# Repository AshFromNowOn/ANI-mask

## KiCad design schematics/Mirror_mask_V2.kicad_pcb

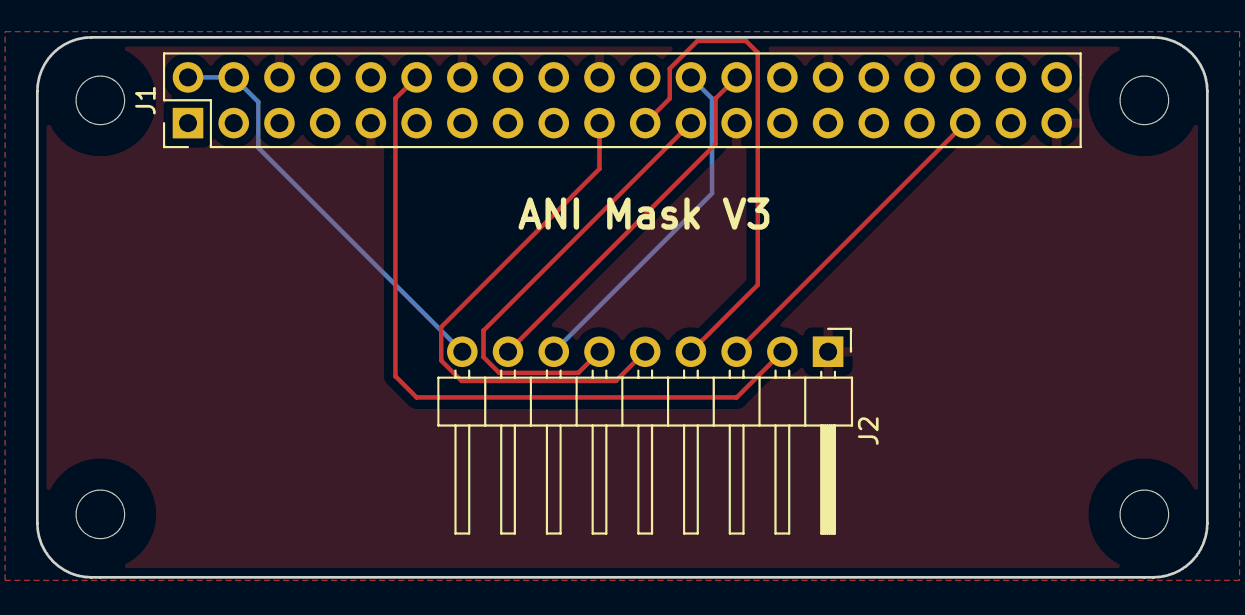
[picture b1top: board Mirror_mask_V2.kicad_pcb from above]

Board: 2 copper layers, 65.0 x 30.0 mm, 6 parts (0 on the bottom side), 9 nets.

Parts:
H1, H2, H3, H4: MountingHole; MountingHole_2.7mm_M2.5_uHAT_RPi
J1: Raspberry_Pi_2_3; PinHeader_2x20_P2.54mm_Vertical
J2: Eyes Connector; PinHeader_1x09_P2.54mm_Horizontal

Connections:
GND: J1.6 (GND), J1.9 (GND), J1.14 (GND), J1.20 (GND), J1.25 (GND), J1.30 (GND), J1.34 (GND), J1.39 (GND), J2.1 (GND)
unnamed: J1.2 (5V), J1.4 (5V), J2.9 (5v)
unnamed: J1.12 (GPIO18/PWM0), J2.2 (BL_0)
unnamed: J1.19 (MOSI0/GPIO10), J2.5 (MOSI)
unnamed: J1.21 (MISO0/GPIO9), J2.4 (DC)
unnamed: J1.23 (SCLK0/GPIO11), J2.6 (SCK)
unnamed: J1.24 (~CE0/GPIO8), J2.7 (CS_0)
unnamed: J1.26 (~CE1/GPIO7), J2.8 (CS_1)
unnamed: J1.35 (GPIO19/MISO1), J2.3 (BL_1)

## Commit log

2022-05-18 added schematics
2022-05-18 reduced SPi speed so it can work on the Pi Zero. Also added Wink option (up and right)
2022-05-18 added heart eyes

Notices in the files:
schematics/Mirror_mask_V2.kicad_pcb:
This PCB design is licensed under MIT Open Source License.
